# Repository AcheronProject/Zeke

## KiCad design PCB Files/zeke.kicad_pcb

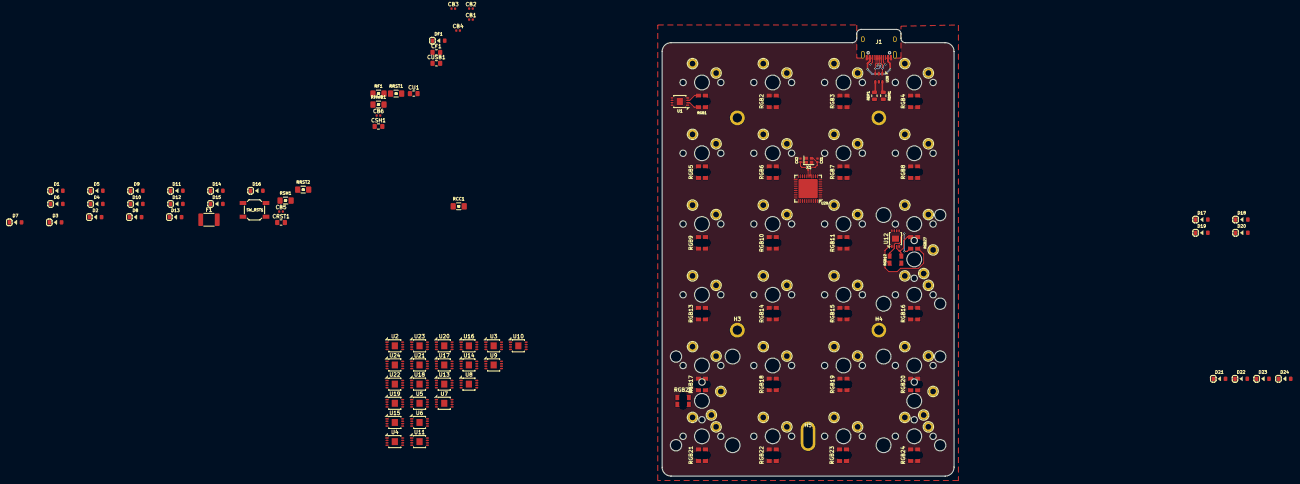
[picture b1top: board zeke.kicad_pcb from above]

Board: 2 copper layers, 78.6 x 120.3 mm, 134 parts (0 on the bottom side), 123 nets.

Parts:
CB1: 1uF; C_0402_1005Metric
CB2, CB3, CB4, CB5, CB6: 100nF; C_0402_1005Metric
CF1: 1u; C_0805_2012Metric_Pad1.15x1.40mm_HandSolder
CRST1: 100nF; C_0805_2012Metric_Pad1.15x1.40mm_HandSolder
CSH1: 100nF; C_0805_2012Metric_Pad1.15x1.40mm_HandSolder
CU1: 1uF; C_0805_2012Metric_Pad1.15x1.40mm_HandSolder
CUSB1: 100nF; C_0805_2012Metric_Pad1.15x1.40mm_HandSolder
CX1, CX2: 8.2pF; C_0402_1005Metric
D1, D2, D3, D4, D5, D6, D7, D8, D9, D10, D11, D12, D13, D14, D15, D16, D17, D18, D19, D20, D21, D22, D23, D24: 1N4148; D_SOD-123
DF1: RB060M-60TR; D_SOD-123
F1: Polyfuse; Fuse_1812_4532Metric_Pad1.30x3.40mm_HandSolder
H1, H2, H3, H4: MountingHole; Mounting_Hole_2.5x04mm
H5: MountingHole; Mounting_Hole_Oval_2.5x8mm
J1: USB_B_Mini; TYPE-C-31-M-12
RCC1: 5.1k; R_SMD_1026
RDM1: 22; R_0805_2012Metric
RDP1: 22; R_0805_2012Metric
RF1: 10k; R_SMD_1026
RGB1, RGB2, RGB3, RGB4, RGB5, RGB6, RGB7, RGB8, RGB9, RGB10, RGB11, RGB12, RGB13, RGB14, RGB15, RGB16, RGB17, RGB18, RGB19, RGB20, RGB21, RGB22, RGB23, RGB24, RGB25, RGB27: LED_GBRA; E6C1209RGB
RHWB1: 1k; R_SMD_1026
RRST1: 4.7k; R_SMD_1026
RRST2: 330R; R_SMD_1026
RSH1: 1M; R_SMD_1026
SW1, SW2, SW3, SW4, SW5, SW6, SW7, SW8, SW9, SW10, SW11, SW12, SW13, SW14, SW15, SW16, SW17, SW18, SW19, SW20, SW21, SW22, SW23, SW24: MXSwitch; MX100
SW25: MXSwitch; MX200R
SW26, SW27: MXSwitch; MX200
SW_RST1: SW_Push; smdPushBtn
U1, U2, U3, U4, U5, U6, U7, U8, U9, U10, U11, U12, U13, U14, U15, U16, U17, U18, U19, U20, U21, U22, U23, U24: WS2811M; MSOP-8-1EP_3x3mm_P0.65mm_EP1.68x1.88mm
U28: USBLC6-2SC6; SOT-23-6
U29: ATMEGA32U4; QFN-44-1EP_7x7mm_P0.5mm_EP5.2x5.2mm
X1: 16MHz; Crystal_SMD_2016-4Pin_2.0x1.6mm

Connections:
5V: CB1.2, CB2.1, CB3.2, CB4.2, CB5.1, CB6.1, CF1.2, CUSB1.1, DF1.1, F1.1, RF1.2, RGB1.4, RGB2.4, RGB3.4, RGB4.4, RGB5.4, RGB6.4, RGB7.4, RGB8.4, RGB9.4, RGB10.4, RGB11.4, RGB12.4, RGB13.4, RGB14.4, RGB15.4, RGB16.4, RGB17.4, RGB18.4, RGB19.4, RGB20.4, RGB21.4, RGB22.4, RGB23.4, RGB24.4, RGB25.4, RGB27.4, RRST1.2, U1.8, U2.8, U3.8, U4.8, U5.8, U6.8, U7.8, U8.8, U9.8, U10.8, U11.8, U12.8, U13.8, U14.8, U15.8, U16.8, U17.8, U18.8, U19.8, U20.8, U21.8, U22.8, U23.8, U24.8, U28.5, U29.2, U29.7, U29.14, U29.24, U29.35, U29.42, U29.44
/RST: CRST1.2, RRST1.1, RRST2.2, U29.13
/SHIELD: CSH1.1, J1.S, RSH1.2
/XTAL1: CX2.1, U29.17, X1.1
/XTAL2: CX1.1, U29.16, X1.3
Col1: SW1.1, SW5.1, SW9.1, SW13.1, SW17.1, SW21.1, SW25.1
Col2: SW2.1, SW6.1, SW10.1, SW14.1, SW18.1, SW22.1
Col3: SW3.1, SW7.1, SW11.1, SW15.1, SW19.1, SW23.1
Col4: SW4.1, SW8.1, SW12.1, SW16.1, SW20.1, SW24.1, SW26.1, SW27.1
DBusN: J1.A7, J1.B7, U28.1
DBusP: J1.A6, J1.B6, U28.3
DN: RDM1.2, U29.3
DP: RDP1.1, U29.4
GND: CB1.1, CB2.2, CB3.1, CB4.1, CB5.2, CB6.2, CF1.1, CRST1.1, CSH1.2, CU1.2, CUSB1.2, CX1.2, CX2.2, DF1.2, J1.A1, J1.B1, RCC1.2, RF1.1, RHWB1.1, RSH1.1, SW_RST1.1, U1.4, U2.4, U3.4, U4.4, U5.4, U6.4, U7.4, U8.4, U9.4, U10.4, U11.4, U12.4, U13.4, U14.4, U15.4, U16.4, U17.4, U18.4, U19.4, U20.4, U21.4, U22.4, U23.4, U24.4, U28.2, U29.5, U29.15, U29.23, U29.34, U29.43, X1.2, X1.4
unnamed: CU1.1, U29.6
unnamed: D1.2, SW1.2
unnamed: D2.2, SW2.2
unnamed: D3.2, SW3.2
unnamed: D4.2, SW4.2
unnamed: D5.2, SW5.2
unnamed: D6.2, SW6.2
unnamed: D7.2, SW7.2
unnamed: D8.2, SW8.2
unnamed: D9.2, SW9.2
unnamed: D10.2, SW10.2
unnamed: D11.2, SW11.2
unnamed: D12.2, SW12.2
unnamed: D13.2, SW13.2
unnamed: D14.2, SW14.2
unnamed: D15.2, SW15.2
unnamed: D16.2, SW16.2, SW26.2
unnamed: D17.2, SW17.2
unnamed: D18.2, SW18.2
unnamed: D19.2, SW19.2
unnamed: D20.2, SW20.2
unnamed: D21.2, SW21.2, SW25.2
unnamed: D22.2, SW22.2
unnamed: D23.2, SW23.2
unnamed: D24.2, SW24.2, SW27.2
unnamed: F1.2, J1.A4, J1.B4
unnamed: J1.A5, J1.B5, RCC1.1
unnamed: RDM1.1, U28.6
unnamed: RDP1.2, U28.4
unnamed: RGB1.1, U1.2
unnamed: RGB1.2, U1.3
unnamed: RGB1.3, U1.1
unnamed: RGB2.1, U2.2
unnamed: RGB2.2, U2.3
unnamed: RGB2.3, U2.1
unnamed: RGB3.1, U3.2
unnamed: RGB3.2, U3.3
unnamed: RGB3.3, U3.1
unnamed: RGB4.1, U4.2
unnamed: RGB4.2, U4.3
unnamed: RGB4.3, U4.1
unnamed: RGB5.1, U5.2
unnamed: RGB5.2, U5.3
unnamed: RGB5.3, U5.1
unnamed: RGB6.1, U6.2
unnamed: RGB6.2, U6.3
unnamed: RGB6.3, U6.1
unnamed: RGB7.1, U7.2
unnamed: RGB7.2, U7.3
unnamed: RGB7.3, U7.1
unnamed: RGB8.1, U8.2
unnamed: RGB8.2, U8.3
unnamed: RGB8.3, U8.1
unnamed: RGB9.1, U9.2
unnamed: RGB9.2, U9.3
unnamed: RGB9.3, U9.1
unnamed: RGB10.1, U10.2
unnamed: RGB10.2, U10.3
unnamed: RGB10.3, U10.1
unnamed: RGB11.1, U11.2
unnamed: RGB11.2, U11.3
unnamed: RGB11.3, U11.1
unnamed: RGB12.1, RGB27.1, U12.2
unnamed: RGB12.2, RGB27.2, U12.3
unnamed: RGB12.3, RGB27.3, U12.1
unnamed: RGB13.1, U13.2
unnamed: RGB13.2, U13.3
unnamed: RGB13.3, U13.1
unnamed: RGB14.1, U14.2
unnamed: RGB14.2, U14.3
unnamed: RGB14.3, U14.1
unnamed: RGB15.1, U15.2
unnamed: RGB15.2, U15.3
unnamed: RGB15.3, U15.1
unnamed: RGB16.1, U16.2
unnamed: RGB16.2, U16.3
unnamed: RGB16.3, U16.1
unnamed: RGB17.1, RGB25.1, U17.2
unnamed: RGB17.2, RGB25.2, U17.3
unnamed: RGB17.3, RGB25.3, U17.1
unnamed: RGB18.1, U18.2
unnamed: RGB18.2, U18.3
unnamed: RGB18.3, U18.1
unnamed: RGB19.1, U19.2
unnamed: RGB19.2, U19.3
unnamed: RGB19.3, U19.1
unnamed: RGB20.1, U20.2
unnamed: RGB20.2, U20.3
unnamed: RGB20.3, U20.1
unnamed: RGB21.1, U21.2
unnamed: RGB21.2, U21.3
unnamed: RGB21.3, U21.1
unnamed: RGB22.1, U22.2
unnamed: RGB22.2, U22.3
unnamed: RGB22.3, U22.1
unnamed: RGB23.1, U23.2
unnamed: RGB23.2, U23.3
unnamed: RGB23.3, U23.1
unnamed: RGB24.1, U24.2
unnamed: RGB24.2, U24.3
unnamed: RGB24.3, U24.1
unnamed: RHWB1.2, U29.33
unnamed: RRST2.1, SW_RST1.2
RGB_DIN: U1.6, U2.6, U3.6, U4.6, U5.6, U6.6, U7.6, U8.6, U9.6, U10.6, U11.6, U12.6, U13.6, U14.6, U15.6, U16.6, U17.6, U18.6, U19.6, U20.6, U21.6, U22.6, U23.6, U24.6, U29.27
Row1: D1.1, D2.1, D3.1, D4.1
Row2: D5.1, D6.1, D7.1, D8.1
Row3: D9.1, D10.1, D11.1, D12.1
Row4: D13.1, D14.1, D15.1, D16.1
Row5: D17.1, D18.1, D19.1, D20.1, D21.1, D22.1, D23.1, D24.1

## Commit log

2019-07-29 [Update] Placed switches and LEDs
2019-08-02 [Update,Feature] Placed all components, added Zeke logo, new E6C1209RGB footprint
2019-08-02 [Update] Added new footprint for the RGB LEDs with the 3D model, added Acheron Short logo
